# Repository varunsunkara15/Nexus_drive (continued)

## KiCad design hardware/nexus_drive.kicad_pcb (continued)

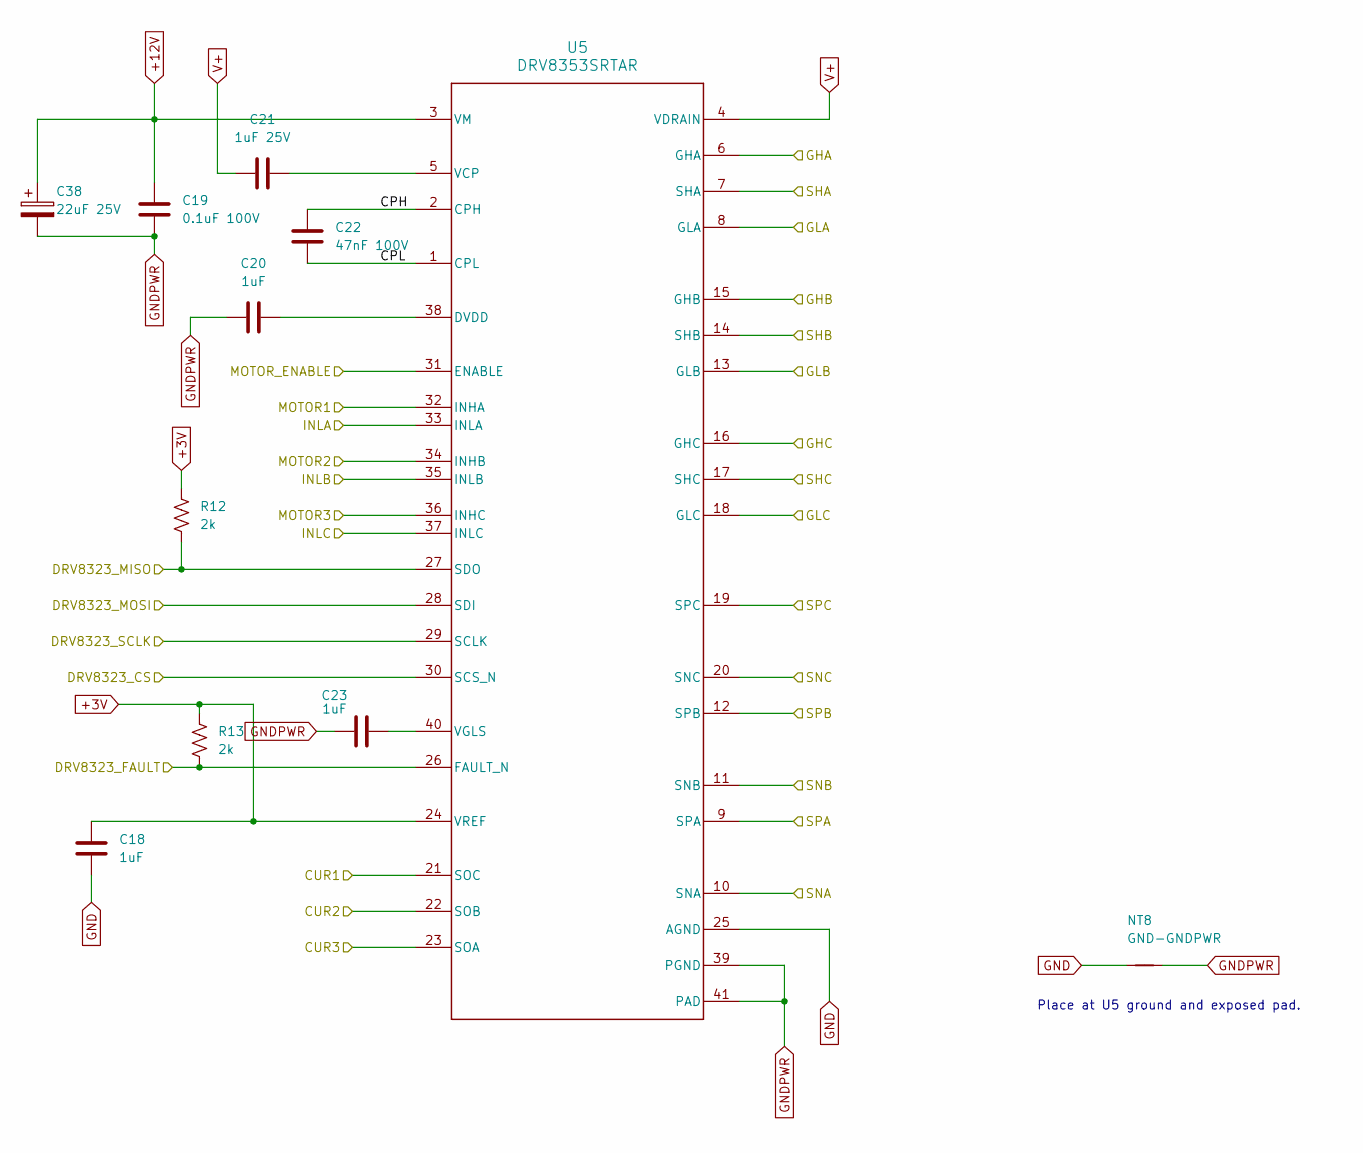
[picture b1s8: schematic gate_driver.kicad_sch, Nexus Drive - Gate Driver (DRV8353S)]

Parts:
C18: 1uF; C_0603_1608Metric; MPN MF-CAP-0603-1uF
C19: 0.1uF 100V; C_0603_1608Metric; MPN GCJ188R72A104KA01D
C20: 1uF; C_0402_1005Metric; MPN MF-CAP-0402-1uF
C21: 1uF 25V; C_0603_1608Metric; MPN C1608X7R1E105K080AE
C22: 47nF 100V; C_0603_1608Metric; MPN C0603X473K1RAC7867
C23: 1uF; C_0603_1608Metric; MPN C1608X7R1E105K080AE
C38: 22uF 25V; CP_Elec_5x5.8; MPN EEEFK1E220AR
NT8: GND-GNDPWR; NetTie-2_SMD_Pad2.0mm
R12, R13: 2k; R_0402_1005Metric; MPN MF-RES-0402-2K
U5: DRV8353SRTAR; RTA0040B; MPN DRV8353SRTAR

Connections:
+3V: C18.2, R12.1, R13.1, U5.24 (VREF); also elsewhere on the board
+12V: C19.2, C38.1, U5.3 (VM)
/CUR1: U5.21 (SOC); also elsewhere on the board
/CUR2: U5.22 (SOB); also elsewhere on the board
/CUR3: U5.23 (SOA); also elsewhere on the board
/DRV_SCLK: U5.29 (SCLK); also elsewhere on the board
/DRV_SDI: U5.28 (SDI); also elsewhere on the board
/DRV_SDO: R12.2, U5.27 (SDO); also elsewhere on the board
/DRV_nCS: U5.30 (SCS_N); also elsewhere on the board
/DRV_nFAULT: R13.2, U5.26 (FAULT_N); also elsewhere on the board
/GATE_EN: U5.31 (ENABLE); also elsewhere on the board
/GHA: U5.6 (GHA); also elsewhere on the board
/GHB: U5.15 (GHB); also elsewhere on the board
/GHC: U5.16 (GHC); also elsewhere on the board
/GLA: U5.8 (GLA); also elsewhere on the board
/GLB: U5.13 (GLB); also elsewhere on the board
/GLC: U5.18 (GLC); also elsewhere on the board
/Gate Driver/CPH: C22.2, U5.2 (CPH)
/Gate Driver/CPL: C22.1, U5.1 (CPL)
/PWM_AH: U5.32 (INHA); also elsewhere on the board
/PWM_AL: U5.33 (INLA); also elsewhere on the board
/PWM_BH: U5.34 (INHB); also elsewhere on the board
/PWM_BL: U5.35 (INLB); also elsewhere on the board
/PWM_CH: U5.36 (INHC); also elsewhere on the board
/PWM_CL: U5.37 (INLC); also elsewhere on the board
/SHA: U5.7 (SHA); also elsewhere on the board
/SHB: U5.14 (SHB); also elsewhere on the board
/SHC: U5.17 (SHC); also elsewhere on the board
/SNA: U5.10 (SNA); also elsewhere on the board
/SNB: U5.11 (SNB); also elsewhere on the board
/SNC: U5.20 (SNC); also elsewhere on the board
/SPA: U5.9 (SPA); also elsewhere on the board
/SPB: U5.12 (SPB); also elsewhere on the board
/SPC: U5.19 (SPC); also elsewhere on the board
GND: C18.1, NT8.1, U5.25 (AGND); also elsewhere on the board
GNDPWR: C19.1, C20.1, C23.1, C38.2, NT8.2, U5.39 (PGND), U5.41 (PAD); also elsewhere on the board
unnamed: C20.2, U5.38 (DVDD)
unnamed: C21.2, U5.5 (VCP)
unnamed: C23.2, U5.40 (VGLS)
V+: C21.1, U5.4 (VDRAIN); also elsewhere on the board

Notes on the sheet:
Place at U5 ground and exposed pad.

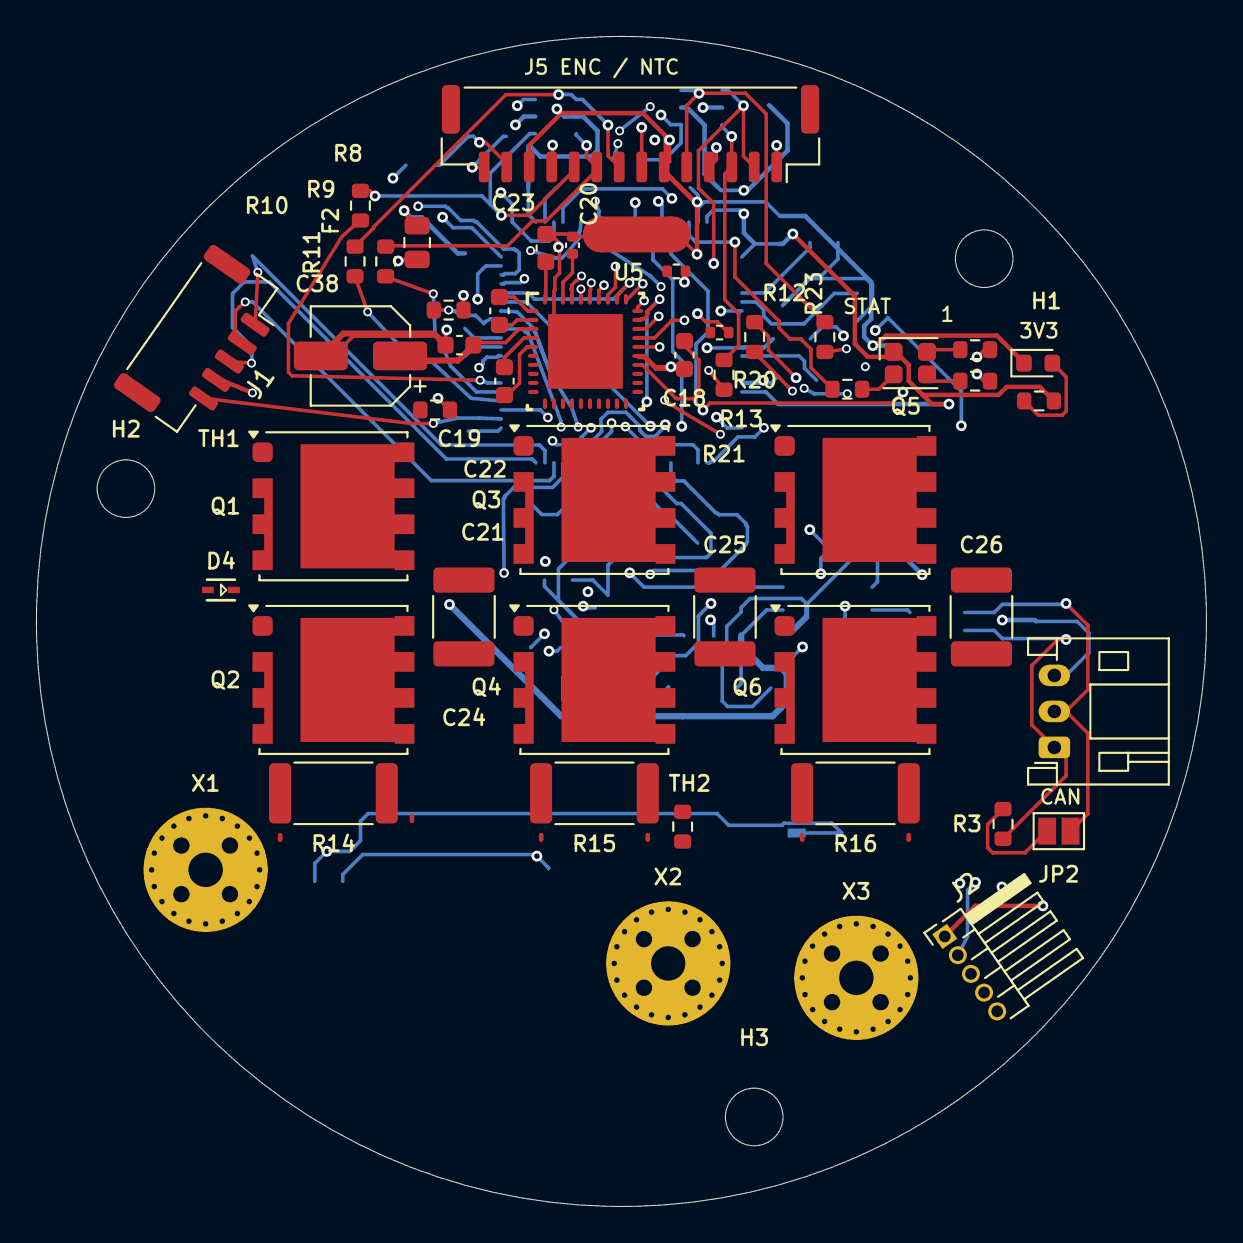
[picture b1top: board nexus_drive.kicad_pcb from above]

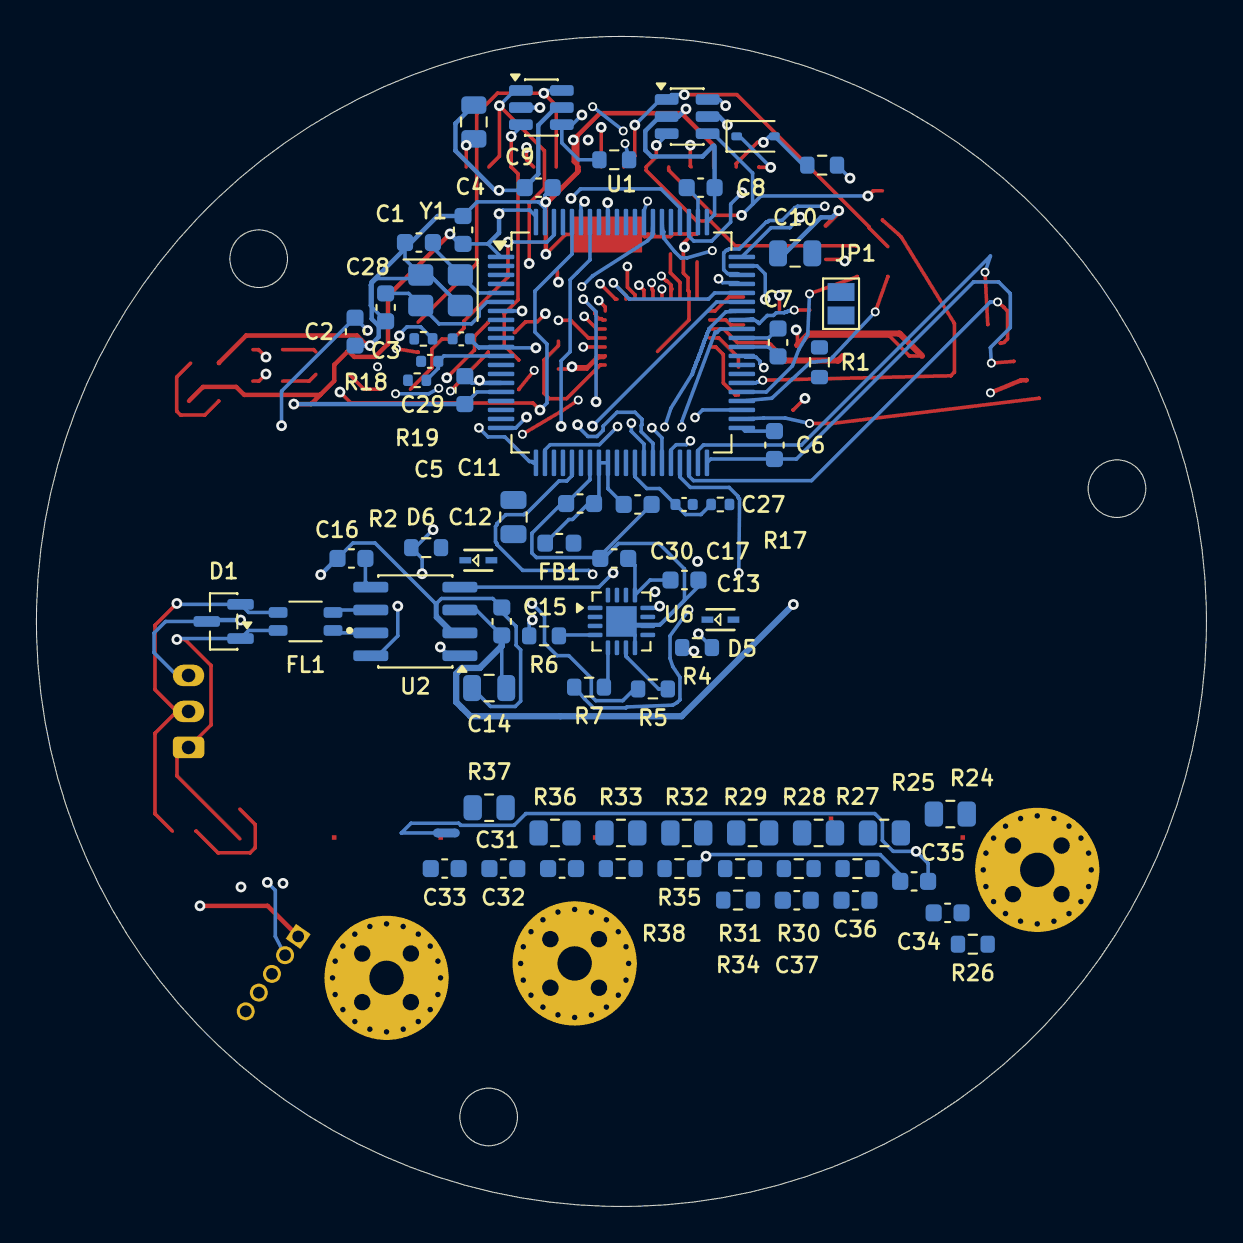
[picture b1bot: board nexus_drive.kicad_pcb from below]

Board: 4 copper layers, 65.0 x 65.0 mm, 127 parts (69 on the bottom side), 111 nets.

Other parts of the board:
H1, H2, H3: MountingHole_3.2mm_M3

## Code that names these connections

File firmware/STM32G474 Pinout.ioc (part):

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board=custom
Mcu.Name=STM32G474M(B-C-E)Tx
Mcu.Package=LQFP80
Mcu.UserName=STM32G474METx
PA0.GPIO_Label=CURR_A
PA0.GPIOParameters=GPIO_Label
PA0.Mode=IN1-Single-Ended
PA0.Signal=ADC1_IN1
PA10.GPIO_Label=PWM_CH
PA10.GPIOParameters=GPIO_Label
PA10.Signal=S_TIM1_CH3
PA11.GPIO_Label=CAN_RX
PA11.GPIOParameters=GPIO_Label
PA11.Mode=FDCAN_Activate
PA11.Signal=FDCAN1_RX
PA12.GPIO_Label=CAN_TX
PA12.GPIOParameters=GPIO_Label
PA12.Mode=FDCAN_Activate
PA12.Signal=FDCAN1_TX
PA13.GPIO_Label=SWDIO
PA13.GPIOParameters=GPIO_Label
PA13.Mode=Serial_Wire
PA13.Signal=SYS_JTMS-SWDIO
PA14.GPIO_Label=SWCLK
PA14.GPIOParameters=GPIO_Label
PA14.Mode=Serial_Wire
PA14.Signal=SYS_JTCK-SWCLK
PA2.GPIO_Label=VBUS
PA2.GPIOParameters=GPIO_Label
PA2.Mode=IN3-Single-Ended
PA2.Signal=ADC1_IN3
PA6.GPIO_Label=SPI1_MISO
PA6.GPIOParameters=GPIO_Label
PA6.Mode=Full_Duplex_Master
PA6.Signal=SPI1_MISO
PA7.GPIO_Label=PWM_AL
PA7.GPIOParameters=GPIO_Label
PA7.Mode=PWM Generation1 CH1 CH1N
PA7.Signal=TIM1_CH1N
PA8.GPIO_Label=PWM_AH
PA8.GPIOParameters=GPIO_Label
PA8.Signal=S_TIM1_CH1
PA9.GPIO_Label=PWM_BH
PA9.GPIOParameters=GPIO_Label
PA9.Signal=S_TIM1_CH2
PB1.GPIO_Label=PWM_CL
PB1.GPIOParameters=GPIO_Label
PB1.Mode=PWM Generation3 CH3 CH3N
PB1.Signal=TIM1_CH3N
PB10.GPIO_Label=USART3_TX
PB10.GPIOParameters=GPIO_Label
PB10.Mode=Asynchronous
PB10.Signal=USART3_TX
PB11.GPIOParameters=GPIO_PuPd,GPIO_Label
PB11.GPIO_Label=HC05_STATE
PB11.GPIO_PuPd=GPIO_PULLDOWN
PB11.Signal=GPIO_Input
PB12.GPIO_Label=DRV_nFAULT
PB12.GPIOParameters=GPIO_Label
PB12.Mode=Activate-Break-Input
PB12.Signal=TIM1_BKIN
PB13.GPIO_Label=SPI2_SCK
PB13.GPIOParameters=GPIO_Label
PB13.Mode=Full_Duplex_Master
PB13.Signal=SPI2_SCK
PB14.GPIO_Label=SPI2_MISO
PB14.GPIOParameters=GPIO_Label
PB14.Mode=Full_Duplex_Master
PB14.Signal=SPI2_MISO
PB15.GPIO_Label=SPI2_MOSI
PB15.GPIOParameters=GPIO_Label
PB15.Mode=Full_Duplex_Master
PB15.Signal=SPI2_MOSI
PB3.GPIO_Label=SPI1_SCK
PB3.GPIOParameters=GPIO_Label
PB3.Mode=Full_Duplex_Master
PB3.Signal=SPI1_SCK
PB5.GPIO_Label=SPI1_MOSI
PB5.GPIOParameters=GPIO_Label
PB5.Mode=Full_Duplex_Master
PB5.Signal=SPI1_MOSI
PB6.GPIOParameters=GPIO_Label,PinState
PB6.GPIO_Label=LED_R
PB6.PinState=GPIO_PIN_SET
PB6.Signal=GPIO_Output
PB7.GPIOParameters=GPIO_Label,PinState
PB7.GPIO_Label=LED_G
PB7.PinState=GPIO_PIN_SET
PB7.Signal=GPIO_Output
PB9.GPIOParameters=GPIO_Label,PinState
PB9.GPIO_Label=LED_B
PB9.PinState=GPIO_PIN_SET
PB9.Signal=GPIO_Output
PC0.GPIO_Label=VPH_A
PC0.GPIOParameters=GPIO_Label
PC0.Mode=IN6-Single-Ended
PC0.Signal=ADC1_IN6
PC1.GPIO_Label=VPH_B
PC1.GPIOParameters=GPIO_Label
PC1.Mode=IN7-Single-Ended
PC1.Signal=ADC2_IN7
PC10.GPIO_Label=SPI3_SCK
PC10.GPIOParameters=GPIO_Label
PC10.Mode=Full_Duplex_Master
PC10.Signal=SPI3_SCK
PC11.GPIO_Label=SPI3_MISO
PC11.GPIOParameters=GPIO_Label
PC11.Mode=Full_Duplex_Master
PC11.Signal=SPI3_MISO
PC12.GPIO_Label=SPI3_MOSI
PC12.GPIOParameters=GPIO_Label
PC12.Mode=Full_Duplex_Master
PC12.Signal=SPI3_MOSI
PC2.GPIO_Label=VPH_C
PC2.GPIOParameters=GPIO_Label
PC2.Mode=IN8-Single-Ended
PC2.Signal=ADC2_IN8
PC3.GPIO_Label=CURR_B
PC3.GPIOParameters=GPIO_Label
PC3.Mode=IN9-Single-Ended
PC3.Signal=ADC2_IN9
PC4.GPIO_Label=GATE_EN
PC4.GPIOParameters=GPIO_Label,PinState
PC4.PinState=GPIO_PIN_RESET
PC4.Signal=GPIO_Output
PC6.GPIO_Label=ENC1_CS
PC6.GPIOParameters=GPIO_Label,PinState
PC6.PinState=GPIO_PIN_SET
PC6.Signal=GPIO_Output
PC7.GPIO_Label=ENC2_CS
PC7.GPIOParameters=GPIO_Label,PinState
PC7.PinState=GPIO_PIN_SET
PC7.Signal=GPIO_Output
PC8.GPIO_Label=ENC3_CS
PC8.GPIOParameters=GPIO_Label,PinState
PC8.PinState=GPIO_PIN_SET
PC8.Signal=GPIO_Output
PC9.GPIO_Label=CAN_STB
PC9.GPIOParameters=GPIO_Label,PinState
PC9.PinState=GPIO_PIN_SET
PC9.Signal=GPIO_Output
PD10.GPIO_Label=DRV_nCS
PD10.GPIOParameters=GPIO_Label,PinState
PD10.PinState=GPIO_PIN_SET
PD10.Signal=GPIO_Output
PD8.GPIO_Label=TEMP_FET_LS
PD8.GPIOParameters=GPIO_Label
PD8.Mode=IN12-Single-Ended
PD8.Signal=ADC4_IN12
PE10.GPIO_Label=PWM_BL
PE10.GPIOParameters=GPIO_Label
PE10.Mode=PWM Generation2 CH2 CH2N
PE10.Signal=TIM1_CH2N
PE11.GPIO_Label=TEMP_MOTOR
PE11.GPIOParameters=GPIO_Label
PE11.Mode=IN15-Single-Ended
PE11.Signal=ADC4_IN15
PE12.GPIO_Label=DRV_SCLK
PE12.GPIOParameters=GPIO_Label
PE12.Mode=Full_Duplex_Master
PE12.Signal=SPI4_SCK
PE13.GPIO_Label=DRV_SDO
PE13.GPIOParameters=GPIO_Label
PE13.Mode=Full_Duplex_Master
PE13.Signal=SPI4_MISO
PE14.GPIO_Label=DRV_SDI
PE14.GPIOParameters=GPIO_Label
PE14.Mode=Full_Duplex_Master
PE14.Signal=SPI4_MOSI
PE15.GPIO_Label=USART3_RX
PE15.GPIOParameters=GPIO_Label
PE15.Mode=Asynchronous
PE15.Signal=USART3_RX
PE8.GPIO_Label=TEMP_FET_HS
PE8.GPIOParameters=GPIO_Label
PE8.Mode=IN6-Single-Ended
PE8.Signal=ADC4_IN6
PE9.GPIO_Label=CURR_C
PE9.GPIOParameters=GPIO_Label
PE9.Mode=IN2-Single-Ended
PE9.Signal=ADC3_IN2
PF0-OSC_IN.Mode=HSE-External-Oscillator
PF0-OSC_IN.Signal=RCC_OSC_IN
PF1-OSC_OUT.Mode=HSE-External-Oscillator
PF1-OSC_OUT.Signal=RCC_OSC_OUT
RCC.HSE_VALUE=16000000
RCC.SYSCLKFreq_VALUE=160000000
RCC.SYSCLKSource=RCC_SYSCLKSOURCE_PLLCLK
